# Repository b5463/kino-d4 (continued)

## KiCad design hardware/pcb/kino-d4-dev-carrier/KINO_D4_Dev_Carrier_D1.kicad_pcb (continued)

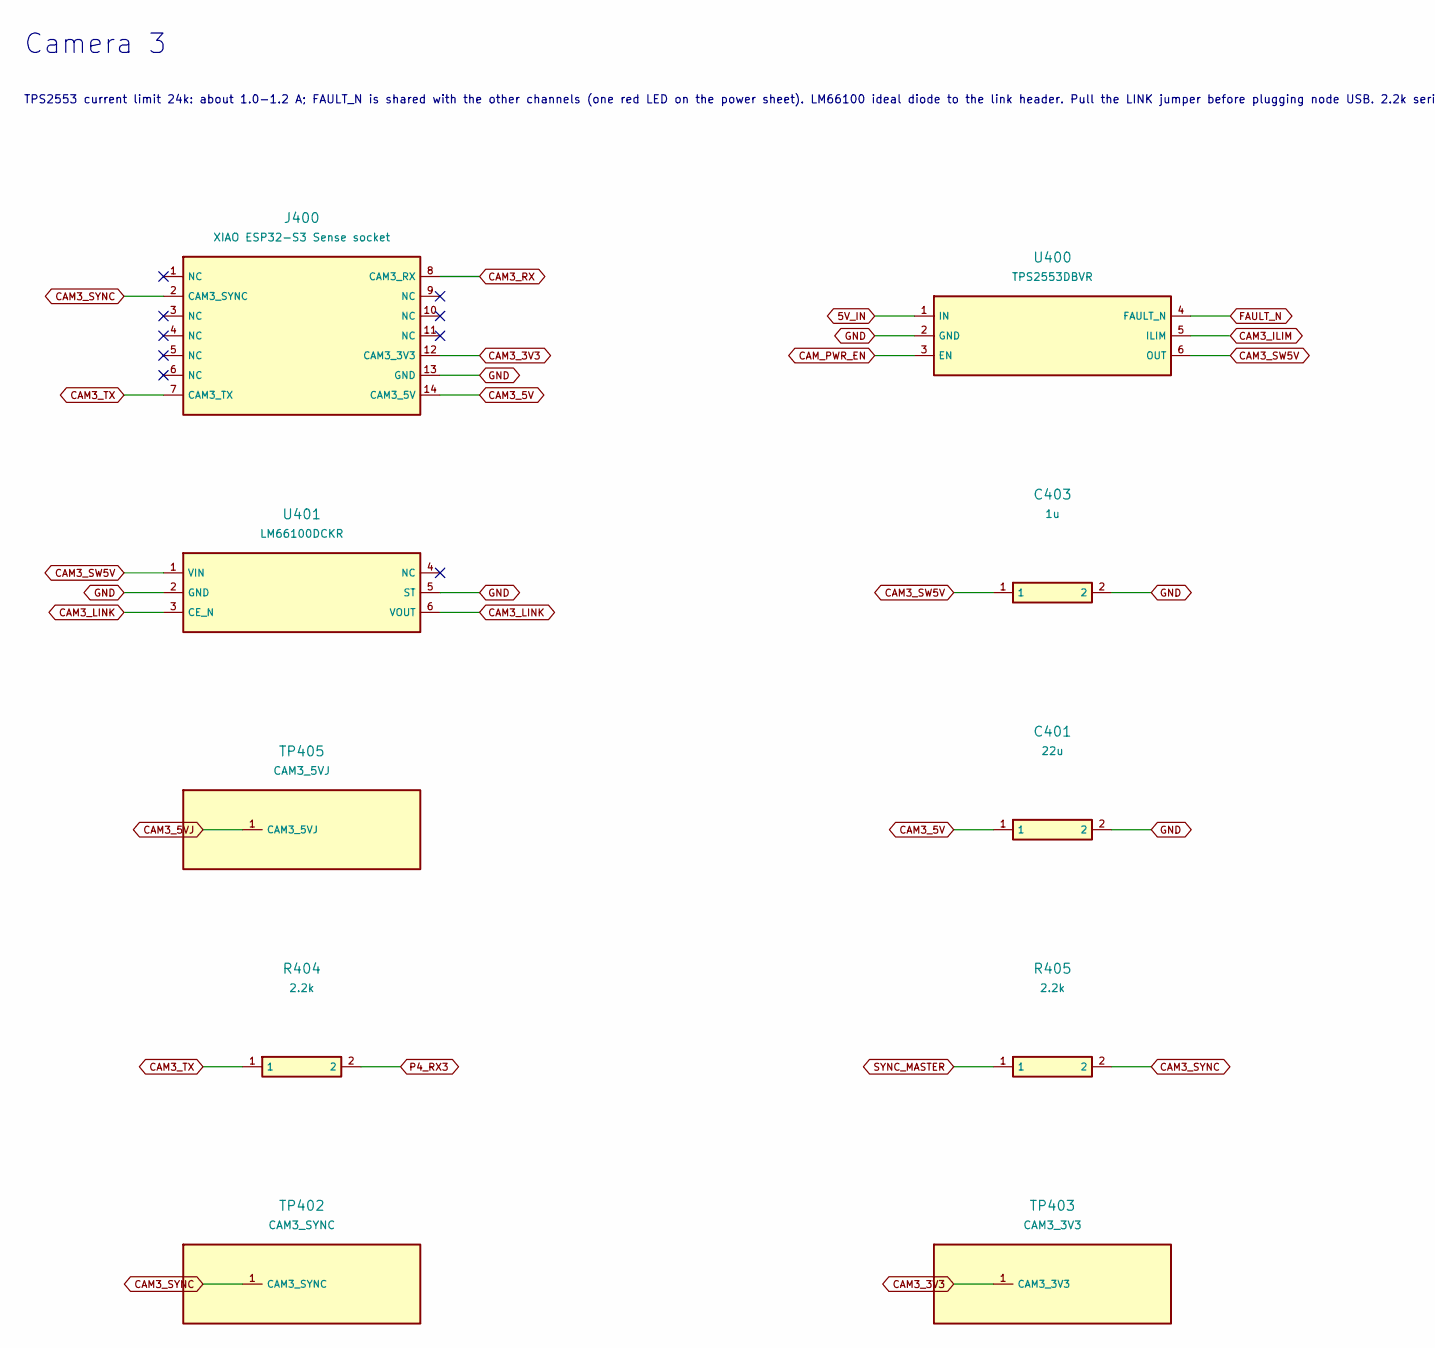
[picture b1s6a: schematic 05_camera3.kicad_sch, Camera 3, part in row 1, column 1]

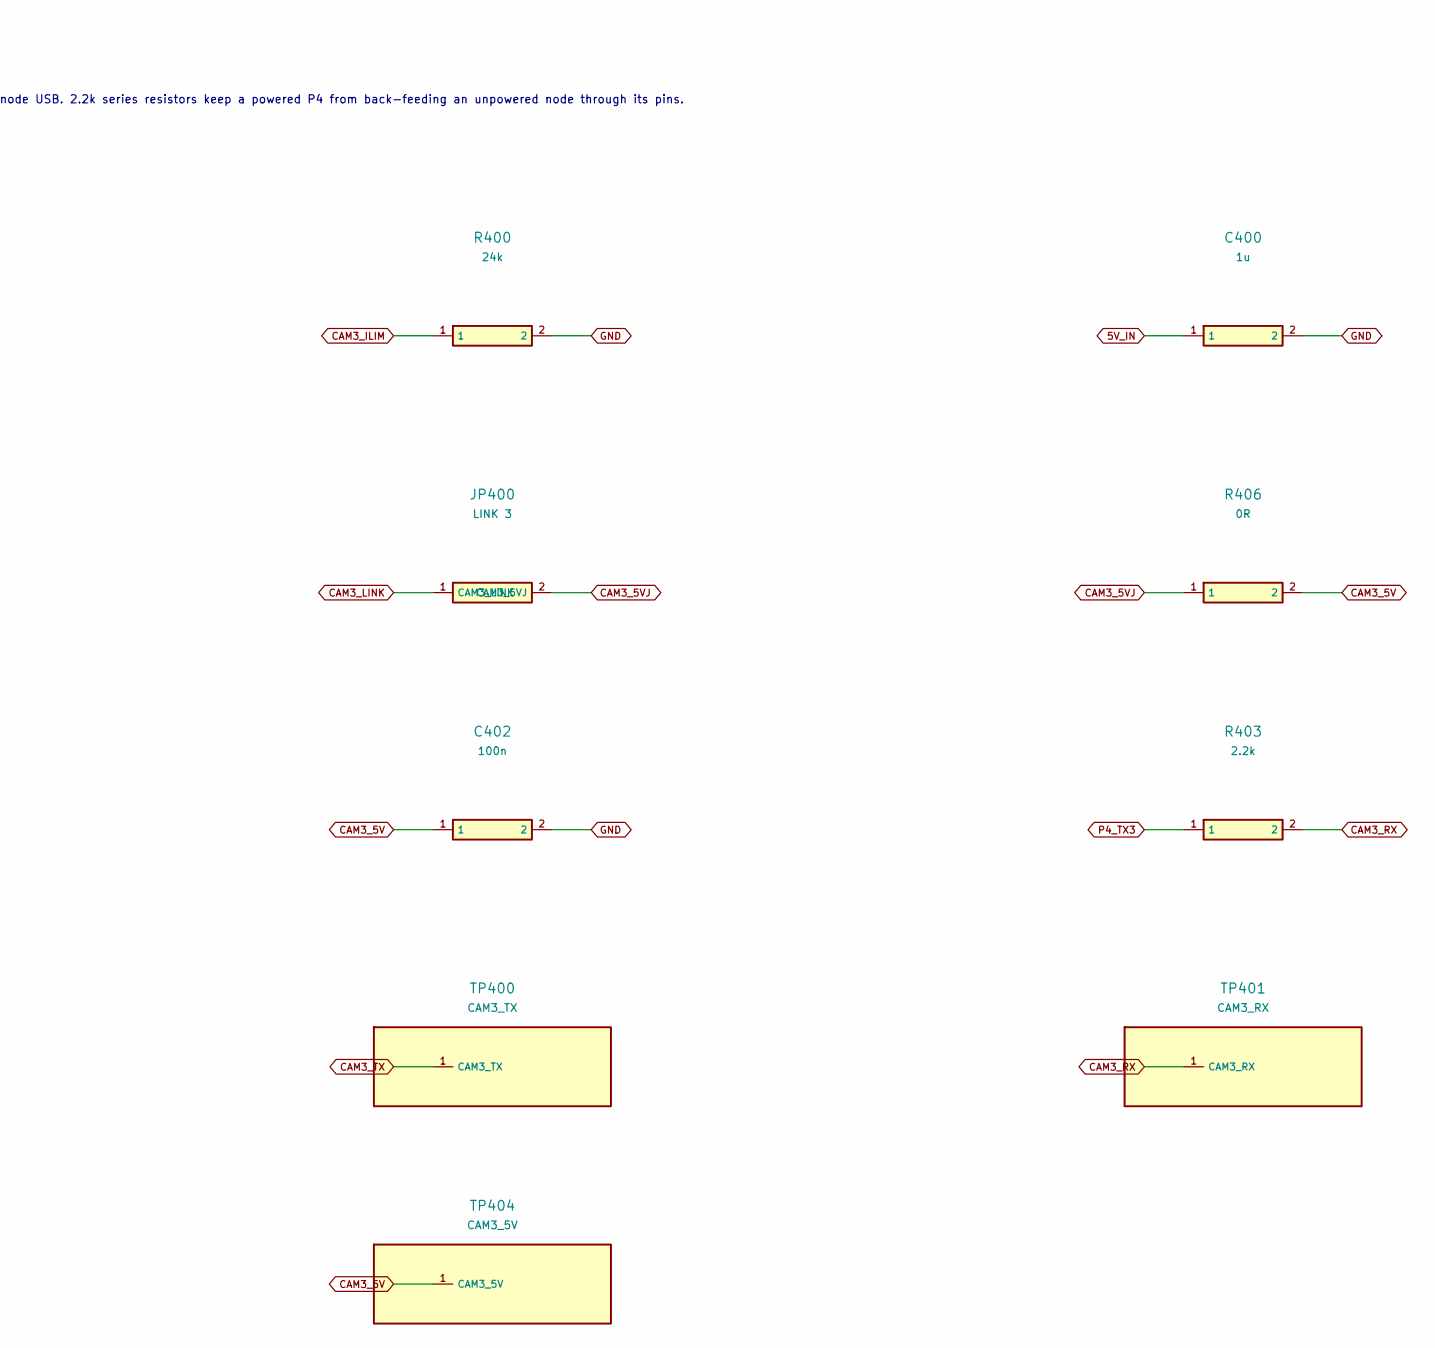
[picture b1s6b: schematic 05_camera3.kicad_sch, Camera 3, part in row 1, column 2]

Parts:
C400, C403: 1u; C_0603_1608Metric; LCSC C15849
C401: 22u; C_0805_2012Metric; LCSC C45783
C402: 100n; C_0603_1608Metric; LCSC C14663
J400: XIAO ESP32-S3 Sense socket; XIAO_Socket_15.24mm
JP400: LINK 3; PinHeader_1x02_P2.54mm_Vertical
R400: 24k; R_0603_1608Metric; LCSC C23352
R403, R404, R405: 2.2k; R_0603_1608Metric; LCSC C4190
R406: 0R; R_0603_1608Metric; LCSC C21189
TP400: CAM3_TX; TestPoint_Pad_D1.5mm
TP401: CAM3_RX; TestPoint_Pad_D1.5mm
TP402: CAM3_SYNC; TestPoint_Pad_D1.5mm
TP403: CAM3_3V3; TestPoint_Pad_D1.5mm
TP404: CAM3_5V; TestPoint_Pad_D1.5mm
TP405: CAM3_5VJ; TestPoint_Pad_D1.5mm
U400: TPS2553DBVR; SOT-23-6; LCSC C55266
U401: LM66100DCKR; SOT-363_SC-70-6; LCSC C2869734

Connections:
5V_IN: C400.1, U400.1 (IN); also elsewhere on the board
CAM3_3V3: J400.12 (CAM3_3V3), TP403.1
CAM3_5V: C401.1, C402.1, J400.14 (CAM3_5V), R406.2, TP404.1
CAM3_5VJ: JP400.2 (CAM3_5VJ), R406.1, TP405.1
CAM3_ILIM: R400.1, U400.5 (ILIM)
CAM3_LINK: JP400.1 (CAM3_LINK), U401.3 (CE_N), U401.6 (VOUT)
CAM3_RX: J400.8 (CAM3_RX), R403.2, TP401.1
CAM3_SW5V: C403.1, U400.6 (OUT), U401.1 (VIN)
CAM3_SYNC: J400.2 (CAM3_SYNC), R405.2, TP402.1
CAM3_TX: J400.7 (CAM3_TX), R404.1, TP400.1
CAM_PWR_EN: U400.3 (EN); also elsewhere on the board
FAULT_N: U400.4 (FAULT_N); also elsewhere on the board
GND: C400.2, C401.2, C402.2, C403.2, J400.13 (GND), R400.2, U400.2 (GND), U401.2 (GND), U401.5 (ST); also elsewhere on the board
P4_RX3: R404.2; also elsewhere on the board
P4_TX3: R403.1; also elsewhere on the board
SYNC_MASTER: R405.1; also elsewhere on the board

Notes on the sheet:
Camera 3
TPS2553 current limit 24k: about 1.0-1.2 A; FAULT_N is shared with the other channels (one red LED on the power sheet). LM66100 ideal diode to the link header. Pull the LINK jumper before plugging node USB. 2.2k series resistors keep a powered P4 from back-feeding an unpowered node through its pins.

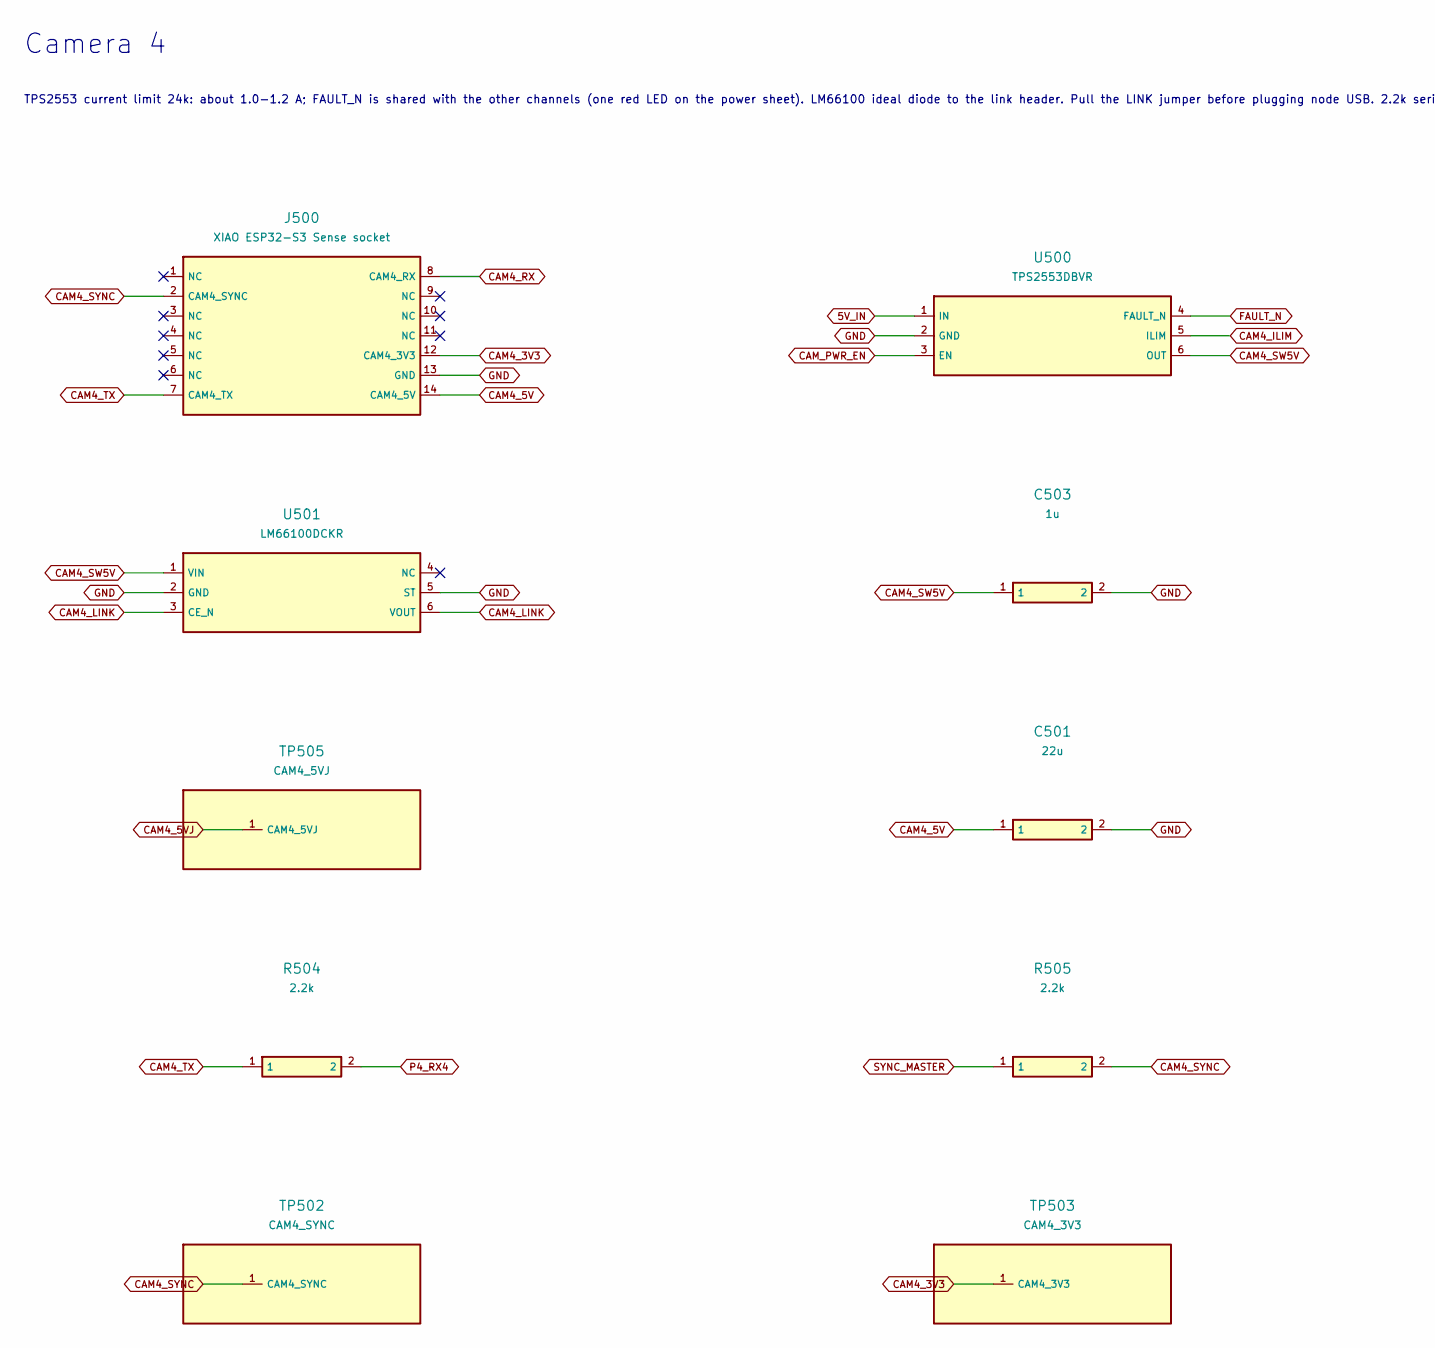
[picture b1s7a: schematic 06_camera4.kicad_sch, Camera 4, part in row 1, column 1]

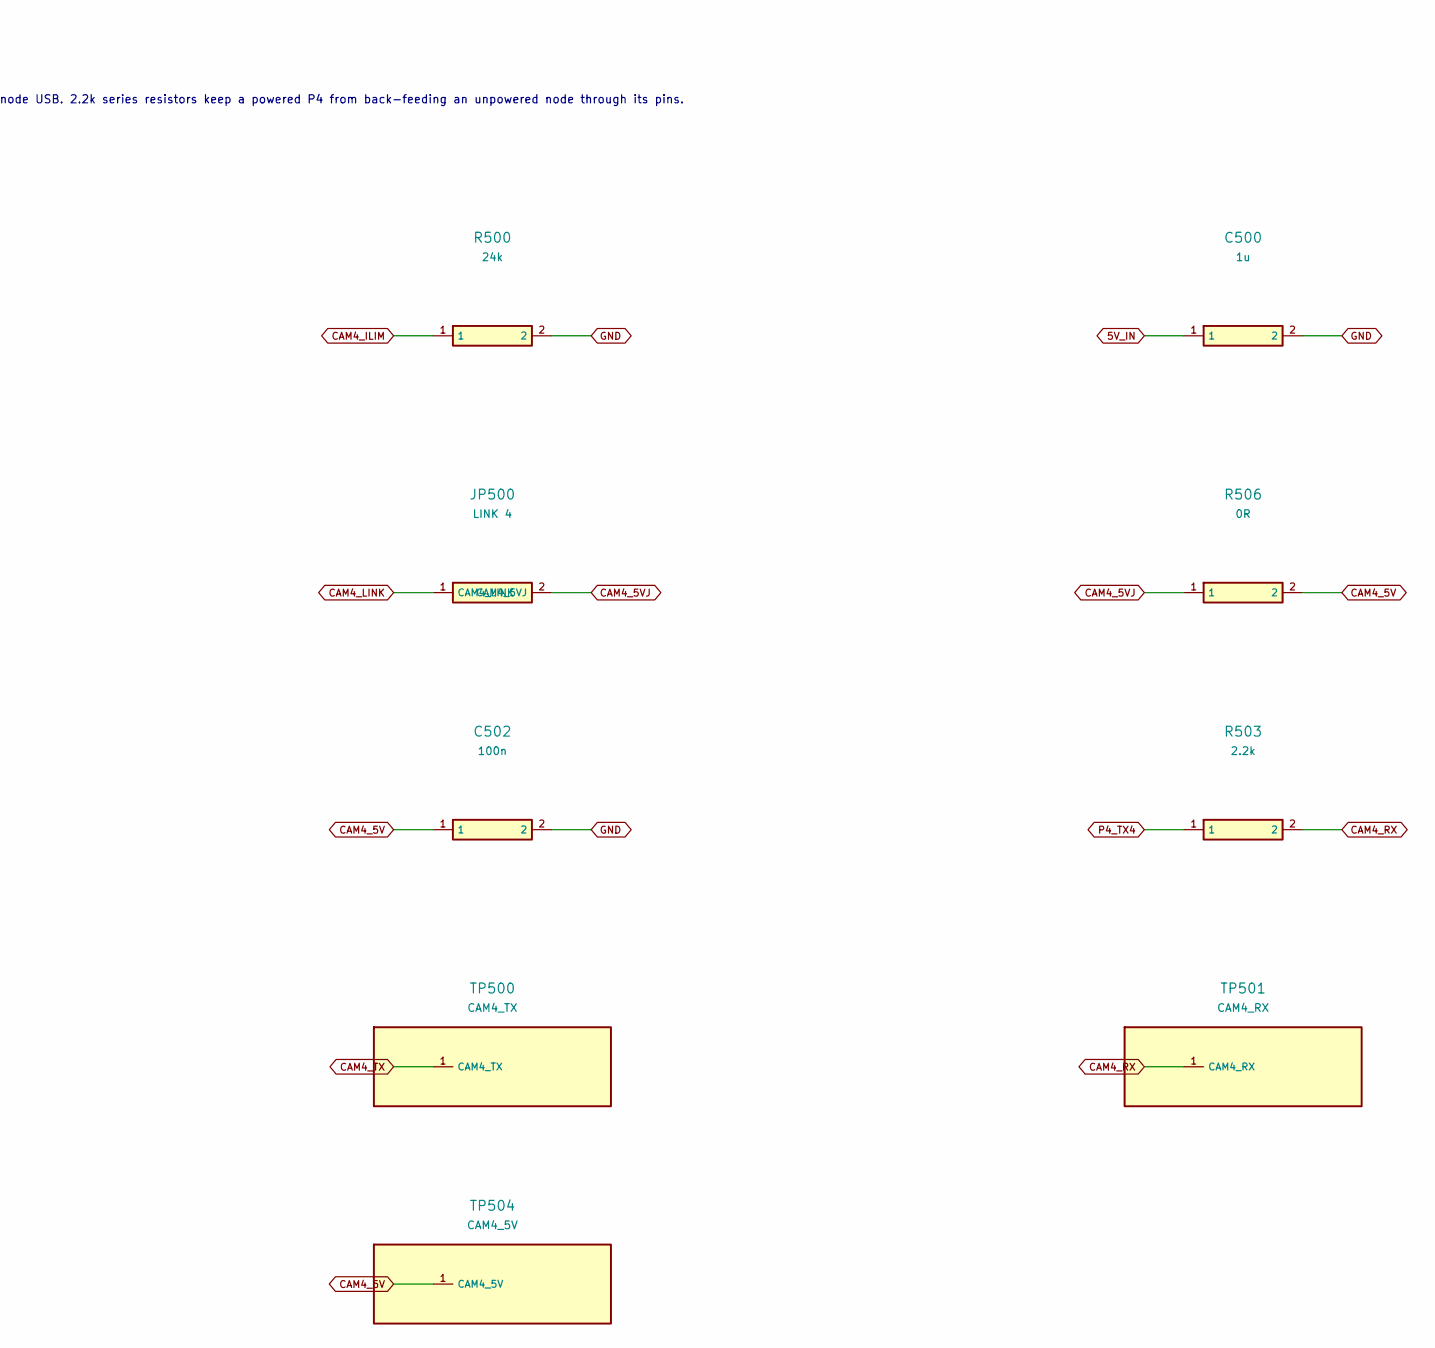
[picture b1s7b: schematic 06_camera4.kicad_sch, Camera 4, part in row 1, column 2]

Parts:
C500, C503: 1u; C_0603_1608Metric; LCSC C15849
C501: 22u; C_0805_2012Metric; LCSC C45783
C502: 100n; C_0603_1608Metric; LCSC C14663
J500: XIAO ESP32-S3 Sense socket; XIAO_Socket_15.24mm
JP500: LINK 4; PinHeader_1x02_P2.54mm_Vertical
R500: 24k; R_0603_1608Metric; LCSC C23352
R503, R504, R505: 2.2k; R_0603_1608Metric; LCSC C4190
R506: 0R; R_0603_1608Metric; LCSC C21189
TP500: CAM4_TX; TestPoint_Pad_D1.5mm
TP501: CAM4_RX; TestPoint_Pad_D1.5mm
TP502: CAM4_SYNC; TestPoint_Pad_D1.5mm
TP503: CAM4_3V3; TestPoint_Pad_D1.5mm
TP504: CAM4_5V; TestPoint_Pad_D1.5mm
TP505: CAM4_5VJ; TestPoint_Pad_D1.5mm
U500: TPS2553DBVR; SOT-23-6; LCSC C55266
U501: LM66100DCKR; SOT-363_SC-70-6; LCSC C2869734

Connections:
5V_IN: C500.1, U500.1 (IN); also elsewhere on the board
CAM4_3V3: J500.12 (CAM4_3V3), TP503.1
CAM4_5V: C501.1, C502.1, J500.14 (CAM4_5V), R506.2, TP504.1
CAM4_5VJ: JP500.2 (CAM4_5VJ), R506.1, TP505.1
CAM4_ILIM: R500.1, U500.5 (ILIM)
CAM4_LINK: JP500.1 (CAM4_LINK), U501.3 (CE_N), U501.6 (VOUT)
CAM4_RX: J500.8 (CAM4_RX), R503.2, TP501.1
CAM4_SW5V: C503.1, U500.6 (OUT), U501.1 (VIN)
CAM4_SYNC: J500.2 (CAM4_SYNC), R505.2, TP502.1
CAM4_TX: J500.7 (CAM4_TX), R504.1, TP500.1
CAM_PWR_EN: U500.3 (EN); also elsewhere on the board
FAULT_N: U500.4 (FAULT_N); also elsewhere on the board
GND: C500.2, C501.2, C502.2, C503.2, J500.13 (GND), R500.2, U500.2 (GND), U501.2 (GND), U501.5 (ST); also elsewhere on the board
P4_RX4: R504.2; also elsewhere on the board
P4_TX4: R503.1; also elsewhere on the board
SYNC_MASTER: R505.1; also elsewhere on the board

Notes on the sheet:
Camera 4
TPS2553 current limit 24k: about 1.0-1.2 A; FAULT_N is shared with the other channels (one red LED on the power sheet). LM66100 ideal diode to the link header. Pull the LINK jumper before plugging node USB. 2.2k series resistors keep a powered P4 from back-feeding an unpowered node through its pins.

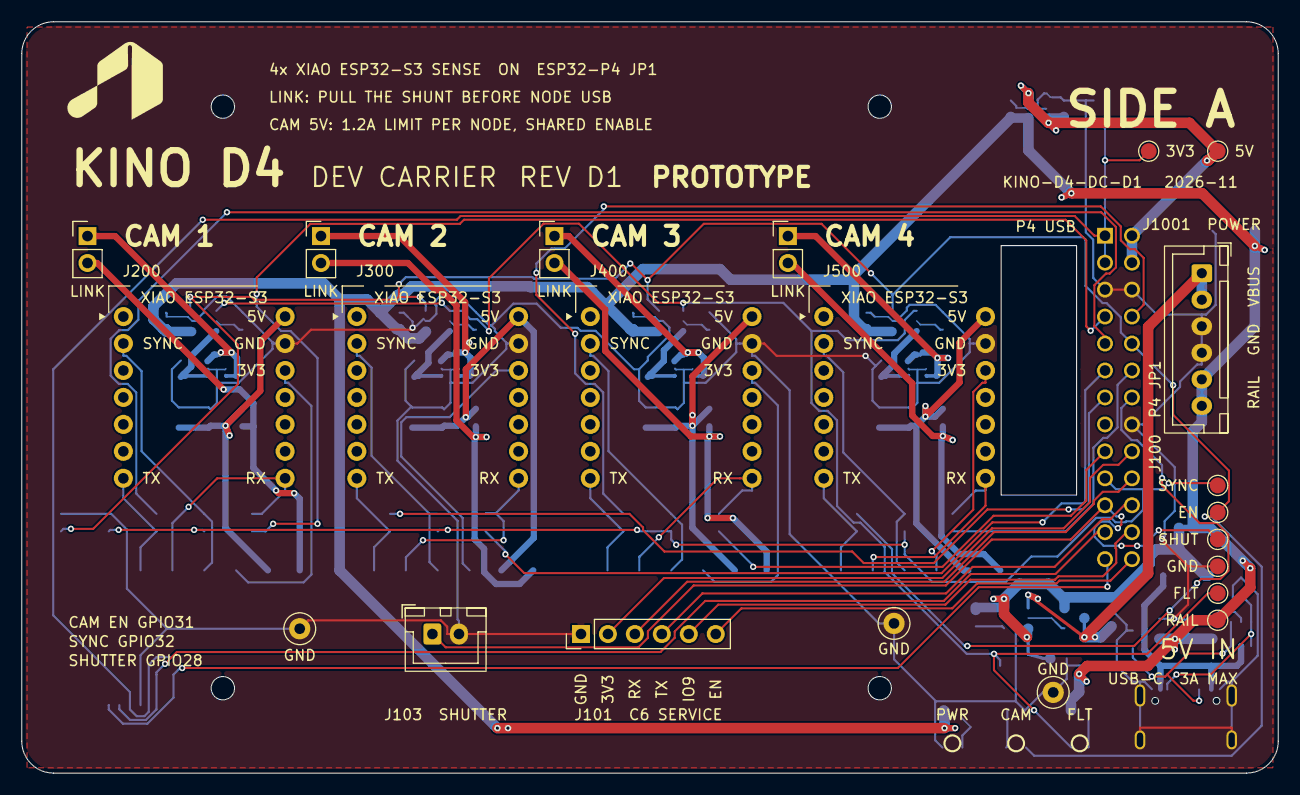
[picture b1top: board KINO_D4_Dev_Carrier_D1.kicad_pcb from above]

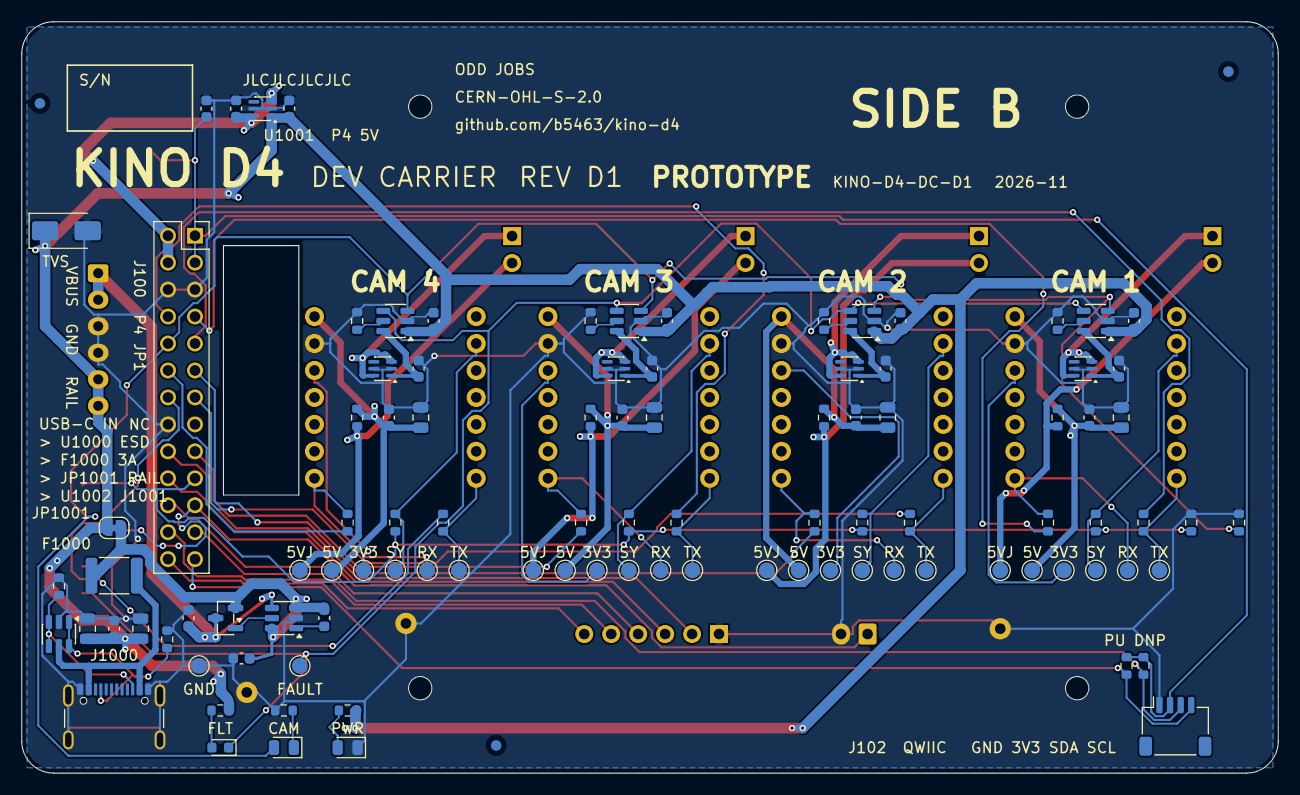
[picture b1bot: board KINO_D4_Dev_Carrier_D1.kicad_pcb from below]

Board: 2 copper layers, 118.4 x 70.8 mm, 130 parts (104 on the bottom side), 69 nets.

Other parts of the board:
H1, H2, H3, H4: M2; MountingHole_2.2mm_M2

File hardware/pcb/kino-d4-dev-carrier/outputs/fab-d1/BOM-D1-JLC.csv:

Comment,Designator,Footprint,LCSC Part #,Manufacturer Part,Quantity,JLC library
100n,"C100,C1002,C202,C302,C402,C502",C_0603_1608Metric,C14663,CC0603KRX7R9BB104,6,basic
22u,"C1000,C1001,C201,C301,C401,C501",C_0805_2012Metric,C45783,CL21A226MAQNNNE,6,basic
1u,"C1005,C1006,C1007,C1003,C1004,C200,C203,C300,C303,C400,C403,C500,C503",C_0603_1608Metric,C15849,CL10A105KB8NNNC,13,basic
LED green,"D1000,D1001",LED_0805_2012Metric,C2297,KT-0805G,2,basic
LED red,D1002,LED_0603_1608Metric,C2286,KT-0603R,1,basic
SMAJ5.0A,D1003,D_SMA,C10758,SMAJ5.0A,1,extended
USB-C 5V,J1000,USB_C_GCT_USB4105_KINO_GND0.05,C3020560,GCT USB4105-GF-A,1,extended
QWIIC 3V3 I2C,J102,JST_SH_SM04B-SRSS-TB_1x04-1MP_P1.00mm_Horizontal,C160404,SM04B-SRSS-TB(LF)(SN),1,extended
IRLML0030TRPBF,Q1000,SOT-23,C67272,IRLML0030TRPBF,1,extended
4.7k,"R100,R101",R_0603_1608Metric,C23162,0603WAF4701T5E,2,basic
5.1k,"R1000,R1001",R_0603_1608Metric,C23186,0603WAF5101T5E,2,basic
1k,"R1002,R1004",R_0603_1608Metric,C21190,0603WAF1001T5E,2,basic
470R,R1003,R_0603_1608Metric,C23179,0603WAF4700T5E,1,basic
24k,"R200,R300,R400,R500",R_0603_1608Metric,C23352,0603WAF2402T5E,4,basic
2.2k,"R203,R204,R205,R303,R304,R305,R403,R404,R405,R503,R504,R505",R_0603_1608Metric,C4190,0603WAF2201T5E,12,basic
0R,"R206,R306,R406,R506",R_0603_1608Metric,C21189,0603WAF0000T5E,4,basic
USBLC6-2SC6,U1000,SOT-23-6,C7519,USBLC6-2SC6,1,extended
LM66100DCKR,"U1001,U201,U301,U401,U501",SOT-363_SC-70-6,C2869734,LM66100DCKR,5,extended
LM74700QDBVRQ1,U1002,SOT-23-6,C2941042,LM74700QDBVRQ1,1,extended
TPS2553DBVR,"U200,U300,U400,U500",SOT-23-6,C55266,TPS2553DBVR,4,extended

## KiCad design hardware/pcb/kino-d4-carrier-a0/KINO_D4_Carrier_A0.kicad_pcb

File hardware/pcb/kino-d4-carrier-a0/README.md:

# KINO D4 carrier A0.2

**Release candidate, 3 October 2026: READY FOR FABRICATION WITH SPECIFIC MANUAL CHECKS.** Fully routed; DRC, ERC and schematic parity clean. Do the checks listed in the [release review](A02-RELEASE.md) before ordering.

Open [KINO_D4_Carrier_A0_2.kicad_pcb](KINO_D4_Carrier_A0_2.kicad_pcb) with its matching project settings. This is the current working board. The supplied [ODD JOBS standard](ODD-JOBS-STANDARD.txt) governs release. The [release review](A02-RELEASE.md) holds the release matrix, the manual checks and the bring-up tests; the 30 September [engineering review](A02-REVIEW.md) is superseded history.

The board has 256 footprints: 80 on the front and 176 on the back, six of them board-only fiducials (three per face). The front carries the four XIAO sockets, the J600 pogo field, the TP100 and TP600-TP602 probe lands, J1100, J1000 and low SMD parts only, so the socketed XIAOs are the tallest parts on it; every cable connector and pin header (J100, J101, J102, J201-J501, J601, J800, J900-J904, J1300) is on the back, the P4 side. The four XIAO sockets keep 22 mm pitch and a 66 mm outer span, with 15.24 mm row centres and 2.54 mm pin pitch. The outline is 117.01 × 69.41 mm. Four 2.2 mm holes target the P4 inner inserts on 61.9 × 54.8 mm centres, with a drawing-derived absolute offset. These XY checks do not validate the assembled enclosure or connector stack.

The [14-sheet schematic](KINO_D4_Carrier_A0.kicad_sch) is the current electrical capture. Historical A0 and A0.1 boards are preserved but no longer match it. Do not use them for fabrication or combine their reports with A0.2.

## Current review files

| File | Purpose |
|---|---|
| [Release review](A02-RELEASE.md) | Release matrix (PASS / FAIL / MANUAL), resolved findings, manual checks before ordering, bring-up tests |
| [Fab package](outputs/fab-a02/) | `fab_a02.py`: Gerbers with job file, Excellon drill, `KINO_D4_Carrier_A0_2-gerbers.zip`, placement file and grouped fab BOM |
| [Assembly front](outputs/A02-ASSEMBLY-FRONT.svg) / [back](outputs/A02-ASSEMBLY-BACK.svg) | References, courtyards and outline; rear view mirrored |
| [Front power detail](outputs/A02-POWER-FRONT.png) / [back power detail](outputs/A02-POWER-BACK.png) | Pack entry, charger and boost region |
| [A0.2 verification](outputs/VERIFICATION-A02.json) / [routing audit](outputs/A02-ROUTING-AUDIT.json) | Counts, geometry and capture-transfer evidence, with board digest |
| [Native DRC](outputs/DRC-A02.json) / [ERC](outputs/ERC-DRAFT.json) | Checker results; no implied manufacturing acceptance |
| [Schematic PDF](outputs/SCHEMATIC-DRAFT.pdf) | 14-sheet capture |
| [BOM](outputs/BOM-DRAFT.csv) / [part selection](design/part_selection.json) / [pin matrix](outputs/PIN_NET_MATRIX.csv) | Manufacturer parts checked against datasheets; battery pack still open |
| [Mounting template](outputs/P4-MOUNTING-TEMPLATE-1TO1.pdf) / [mechanical evidence](MECHANICAL.md) | Print at 100 %; stack and enclosure still unqualified |
| [Printed labels](outputs/A02-PRINTED-LABELS.json) / [assembly references](outputs/A02-ASSEMBLY-LABELS.json) / [unplaced references](outputs/A02-ASSEMBLY-LABELS-UNFINISHED.json) | Label positions; parts without a clear, unambiguous silk position beside the part |
| [Silk text check](outputs/A02-SILK-TEXT.json) | `check_silk_text.py`: text over text, pads, part bodies or silk graphics, crowded or ambiguous references, reading direction |

**Routing status, 3 October 2026 (release pass):** every connection is routed. Native DRC (zones refilled, schematic parity on) reports no violations and no unconnected items; ERC reports none; `verify.py --a02` passes against a freshly exported netlist. 573 vias; 2385 track segments (F 786, In2 414, B 1185). The SYS_RAW battery-to-boost path is now a 3.4-3.9 mm back pour and a 4.6-5.2 mm In2 pour with 19 vias between them and six into L1200 (`power_a02_sys_raw.py`). Five 0.1 mm right-angle wobbles remain inside 0.5-0.8 mm copper (no exposed corner). CAM2_3V3 still takes the long route south of U300 (0.25 mm, light load); CAM_GLOBAL_EN and BOOST_ENABLE are long In2 runs, BOOST_ENABLE now held by R1204 (100k) at the boost end.

Prototype references are on silkscreen (ODD JOBS rule 177) beside their own part: 0.15 mm clear of part outlines, 0.5 mm from other silk text, horizontal text left to right and vertical text bottom to top from its own side (rule 91), 1.0 mm text or 0.8 mm in dense areas, 0.15 mm stroke. A spot more than 0.5 mm nearer another part is not used. After the release pass, 202 of 250 references are on silk; no text overlaps another text, a pad, a part body or a silk graphic (`check_silk_text.py`: 0 findings). The four camera circuits share one offset per role, or the whole group of four goes to Fab. 48 references in the camera, charger and boost clusters (and the DNP R1110) stay on Fab at the part centre and are listed in the unplaced file; they need part spacing, not smaller text. The fiducials keep their references on Fab. Connector, camera and product labels use 1.0 mm text with a 0.15 mm stroke.

## Circuitry

- **Cameras:** four socketed XIAO ESP32-S3 Sense boards with UART/sync isolation buffers, individual current-limited supplies, current monitoring and 0 ohm USB-service power links (JP200-JP500, Vishay CRCW12060000Z0EAHP, desolder before node USB). D8/D9/D10 are shared with the Sense SD interface, and D2 is strap-sensitive.
- **I2C buffer:** U100 (TCA9517) has the carrier bus on its A side, which drives a hard low; the B side's 0.45-0.6 V buffered low faces the P4 bus (P4 VIL 0.825 V). The STUSB4500 (VIL 0.35 V), BQ25798 (0.4 V) and DRV2605L (0.5 V) could not be guaranteed to read the buffered low. Keep the whole bus at 100 kHz (4.7k pull-ups, about 95-150 pF). R100/R101 (2.2k/22k) hold the buffer enable low when JP1 pin 1 is open.
- **P4 link:** the 26-pin P4 connection is a keyed IDC **cable** interface, kept until Guition supplies a JP1 datum for a board-to-board mate. The UART/sync/shutter header map is unchanged; GPIO35/JP1-15 stays unconnected.
- **Power:** USB-C PD sink (STUSB4500), 1S charger (BQ25798), fuel gauge (BQ27441-G1), 5 V boost (TPS61288), 3.3 V buck and a hardware power controller.
  - The USB input survives an unprogrammed STUSB4500, which takes 20 V from a PD charger: D1001 is an SMF22A (22 V standoff), the PD switch FETs are AO4409 (-30 V), R1004 is 10k. Program the NVM for 9 V / 2 A with the 5 V fallback for normal use.
  - The LTC2955-1 EN output is a 2 uA current source; R1204 (100k to SYS_RAW) is the pull-up ADI asks for, so the TPS61288 enable and the PMV16UN load-switch driver (Q1202) see a full logic high.
  - The charger charges whenever VBUS is valid (CE low), inside a 1-60 °C window set by the pack's 103AT-2 thermistor.
  - The gauge shunt is high side, with SRP on the pack side and SRN on the system side.
  - Input current is clamped to 0.15-0.41 A until firmware reads the PD contract, so the board needs its battery to run the P4 and cameras from USB.
  - Off, the board draws 28-46 uA through R1204 plus the controllers' quiescent current.
  - The charger's STAT pin is left open and there is no charge LED (STAT has no layout path out of the charger's power copper). Firmware reads the charge state from the BQ25798 status registers over I2C. The green power LED D1300 stays.
- **Pack entry:** J1100 (JST VH, `- NTC +`) sits on the bottom edge beside the charger. From the pack, F1100 (7 A) and RS700 (5 mΩ) form a 12 mm chain on the front.
- **Sensors and controls:** IMU, backed-up RTC, board-temperature sensor, remote shutter, cover sensor, function button (ESD clamp D903), haptic driver and expansion/service connectors. R105 holds SYNC_MASTER low through the P4's reset.
- **Power links:** JP200-JP500 and JP1200 are 0 ohm links on the front (CRCW1206-HP, 10 A), replacing the 2.54 mm headers and shunts: flat, reachable with the carrier on the P4, rated for the current. Desolder to open.
- **Test field:** J600 is an asymmetric 12-pad **sense/test** field, not a power-injection connector. Do not drive the enable nodes against the expander. Pads 9-11 are unconnected: CAM2_EN, CAM3_EN and CAM4_EN are probed at front lands TP600-TP602 beside their lines at the top of the board (CAM1_EN stays on pad 8). TP100 (P4 3V3 test) is a front land beside J100 pin 1.
- **Expander map:** U600 (TCA9539) port 1, P1.0-P1.7 (pins 13-20): IMU_INT, RTC_INT_N, SOFT_KILL, unused, POWER_INT_N, FN_N, HAPTIC_EN, COVER_N. P1.3 is not connected; configure it as an input. Firmware must follow this map.
- **Flash provision:** J601/R605 are DNP provisions for an **external flash driver**. There is no FLASH_EN GPIO or flash-energy supply.

I2C addresses: PAC1954 0x10, STUSB4500 0x28, TMP117 0x48, RV-3028 0x52, BQ27441 0x55, DRV2605L 0x5A, LSM6DSOX 0x6A, BQ25798 0x6B, TCA9539 0x74. P4 touch at 0x5D stays on the host side of the buffer. [`firmware/p4/main/kino_carrier_a02.h`](../../../firmware/p4/main/kino_carrier_a02.h) holds these addresses, the expander map, the PAC1954 channel map and the charger status field as constants. Existing firmware does not start the carrier's power controls, charger policy or gauge calibration.

## Manufacturing and assembly status

Process: four layers, 1.6 mm, **1 oz copper on all four layers** (set in the board stackup and the Gerber job file; inner 1 oz is not JLCPCB's default), black mask, white silk, ENIG, JLCPCB-class. `design/fab_a02.py` writes the [fab package](outputs/fab-a02/): Gerbers (silk clipped at mask openings) with the job file, Excellon drill (plated and non-plated apart) with maps, one zip for upload, the placement file (both sides, DNP and board-only items left out) and a fab BOM grouped by part number. Fab and assembly notes, the via-in-pad list and the order options are in the [release review](A02-RELEASE.md). Both faces are assembled: the bottom (P4 side) carries most SMD parts including the heavy XAL7070 boost inductor, the XIAO sockets and J1100 are through-hole on the front, the pin headers and J100 through-hole on the back.

Battery selection, retention and the assembled body are not built or verified. The XAL7070 boost inductor (7.0 mm) and the JST VH connector set the tallest parts on their faces. The XIAOs use external antennas; their antenna and cable clearance must be defined in the enclosure. Keep the P4 battery connector unused. USB/P4/carrier source coexistence still needs measurement; the removable power links are service provisions, not automatic backfeed protection.

## Editing and regeneration

The native A0.2 PCB is authoritative for placement and routing. `design/circuit.py` defines the capture and `design/mechanical.py` the envelope and datums. **Do not run the full build or placement seed against current work**: they reset placement and routing.

Change scripts, in the order they were applied:
- **Earlier A0.2 changes:** `rework.py`, `route_a02.py`, `spread_a02_*.py`, `refine_a02_placement.py`, `add_a02_interfaces.py`, `finish_a02.py`.
- **Charger, thermistor and inductors (0.1.8):** `a02_power_rev.py`.
- **Gauge, fuse and CC protection:** `a02_gauge_rev.py`.
- **Pack entry:** `pack_placement.py`, then `route_pack_entry.py`.
- **USB VBUS:** `route_usb_vbus.py`.
- **PMID capacitors:** `route_pmid.py`.
- **Boost supply:** `route_boost_input.py`.
- **Inductor keepouts:** `switch_keepouts.py`.
- **Residual DRC items:** `a02_drc_fixes.py`.
- **Labels:** `pack_labels.py`, `assembly_labels.py --prototype-silk`, then `check_silk_text.py` (exits 1 on any finding). KiCad's silk_overlap check does not compare one footprint's reference with another's.
- **Routing pass, 2 October 2026:**
  1. `route_a02_gaps.py` (charger VBUS corner, U800 supply, boost sense tap), `gnd_stitch.py`.
  2. `grid_router.py` pass, `apply_routes.py`.
  3. `route_a02_charger_escapes.py`: BQ25798 left-column escapes; moves C1119, C1103, C1100, R1104, R1105.
  4. `tidy_a02_dangling.py`, `a02_pad_connections.py`.
  5. `route_a02_sync_bus.py`: SYNC bus from y 19.4 to y 41.05 at the buffers.
  6. `rip_camera_row.py`, then `grid_router.py` with `GR_ORDER=argv` (FAULT_N, EN, REQ, SHUNT_OUT, SYS_5V).
  7. `route_a02_camera_bus.py remove`, `add`, `verify`: In2 control lanes north of the headers.
  8. `place_a02_u600.py place`, `rip`: U600 turned 180 degrees, C601 beside pin 24; `drop_dangling.py`; router.
  9. `place_a02_brand.py`: maker mark moved onto clear pour below J901.
  10. `tidy_routes.py`, run last.
- **External connections to the back, 2 October 2026:**
  1. `place_a02_j100.py place`, `rip`, `add`: J100 on the back in its outline; P4_5V redrawn at 1.2 mm.
  2. `place_a02_backside.py flip`, then `free_spot.py` for J902 and J904, `tofront`, `rip`: headers and JST connectors to the back; the haptic driver cluster, Q1300, R1300, R1301 and R1304 to the front in their place.
  3. `fp_a02_link_1206.py`, `circuit.py` change, `regenerate_capture.py`, netlist / ERC / PDF, `place_a02_links.py`: JP links become 0 ohm links on the front.
  4. `route_a02_p4_feed.py rip`, `add`: P4_5V_ISO as a 2.0 mm In2 run with three vias per layer change.
  5. `clear_a02_backside.py move`, `rip`; `drop_dangling.py`: courtyard and copper conflicts cleared, J601 0.65 mm north.
  6. `place_a02_labels.py`, `assembly_labels.py --prototype-silk`, `check_silk_text.py`: connector labels on the back silkscreen, references beside their parts, silk text check.
- **SYS_5V, 3 October 2026:**
  1. `route_a02_sys5v.py rip`, `add`, `link-rip`, `link-add`: trunk, drops, riser and feed; camera 1 SHUNT_OUT via, IMU_INT middle and the U700 SENSE+ tie removed for it.
  2. `grid_router.py SYS_5V` with `GR_SKIP_REF=U700`, `apply_routes.py`, `tidy_routes.py`: U1201 and J600 branches.
  3. `straighten_a02_j600.py`: the J600 branch as one straight run.
- **Signal pass, 3 October 2026:** `grid_router.py` over every open net except the camera header-socket GPIO, `GR_SKIP_REF=U700`; `apply_routes.py`; `tidy_routes.py`. 195 -> 114 unconnected; six routes at minimum clearance (RTC_BACKUP, P4_SCL, CHARGE_LED_A, CAM3_REQ, MOTOR_N, CAM1_EN) for review. Through-hole pads now also allow 45-degree exits in the router.
- **Camera GPIO, 3 October 2026:** `route_a02_cam_gpio.py clear <k>` for k = 4, 3, 2, 1, DRC and `drop_dangling.py` until stable, then `add <k>`: the eight header-to-socket GPIO lines of each camera as one identical In2 fan-out (eight 1.27 mm lanes, 45-degree fans, no crossings). `plan <k>` reports what is in the way. The nets it opens (camera EN, SYNC, SHUNT_OUT, P4_BUS_EN, MB_3V3 pieces) go back to the grid router.
- **Second router pass, 3 October 2026:** `grid_router.py` over all open nets (`GR_SKIP_REF=U700`), `apply_routes.py`, `tidy_routes.py`: 101 -> 75. P4_BUS_EN is at minimum clearance (review).
- **Ground fixes, 3 October 2026:** five GND pins reached no ground (U900.4/.8 after the haptic driver moved to the front, U701.3, C1101.2, U1201.1). `gnd_stitch.py`; `gnd_pad_vias.py U701.3 'U1201.1>U1201.9'` (U1201 pin 1 to its exposed pad, as in TI's layout); `rip_box.py CHG_REGN 92.5 56.5 97.0 61.0` (a route that circled C1101) then `gnd_pad_vias.py C1101.2` and the router for CHG_REGN; `rip_box.py` for REMOTE_ACTIVE and HAPTIC_REG under U900, `route_a02_u900_gnd.py`, the router for both nets, `gnd_stitch.py`. GND has no open connection; `gnd_islands.py` still lists the U701.3 and U1201.1 fragments because it looks only for a via inside a fragment, not for a track out of it.

- **U700 and Kelvin pairs, 3 October 2026:**
  1. `place_a02_u700.py rip`, `place`: the PAC1954 U700 moves to the front between the camera 2 and 3 headers, centre (58.75, 15.5), with C700 and R700 beside it and C701 on the back; copper on their pads and three runs in the way removed.
  2. `route_a02_kelvin.py clear`, then DRC and `drop_dangling.py --keep <nets with deliberate stubs>` until stable, then `add`: eight 0.15 mm sense lines at 0.32 mm pitch from the inner pad corners of RS200-RS500 to U700, plus U700's GND, MB_3V3 and PAC_ADDR copper. The CAM2_5V and CAM3_5V_ISO vias move. `add` sets the moved vias' nets back, because a save in between can give a via with nothing of its own net attached the pour's net.
  3. `check_a02_kelvin.py`: each sense line touches only its shunt pad and its U700 pin.
  4. `fp_a02_pac1954.py`, `circuit.py` change, `regenerate_capture.py`, netlist / ERC / PDF, `place_a02_u700.py place`: U700 on a project copy of the VQFN-16 land whose pin 1 triangle sits beside the pin 1 corner (the stock one lay on C700's pad).
- **Bus slot, edges and expanders, 3 October 2026** (hand scripts on `handroute.py`; each runs `rip`, `place` where it has one, then `add`, as separate processes):
  1. `route_a02_local_fixes.py`: USB_CC2 out of U1000 (a VBUS via moved), CHG_REGN's missing piece and an In2 link that frees R1107, CHG_TS, POWER_KILL_N under U802 / C803, a straight PACK_FUSED sense exit.
  2. `route_a02_p4_rx4.py`: P4_RX4 back in its F bus lane (y 20.6) with its J100 tap; POWER_INT_N, CAM2_5V and CAM2_5V_ISO cross the band on In2 in one piece; camera 3's 3V3 runs as camera 1's and shares the header row gap with CAM3_FAULT_N at 0.15 mm; TX3, TX1 and RX2 no longer run past their taps.
  3. `place_a02_remote.py dry` / `rip` / `place`, `route_a02_remote.py`: the remote dry-contact chain (D900, R903, R904, C904, U901, C905, R905, Q900) beside J903 and D902 beside J902 (ESD at the connector, ODD JOBS 24).
  4. `route_a02_left_edge.py`: the four C6 service lines up the left edge and along the top edge into J101; SHUTTER_N from Q900 down the left edge on B into J100 pin 21.
  5. `route_a02_u601.py`: C602 beside U601's VCC pin, CAM_GLOBAL_EN tied once under the package, CAM1_EN, CAM3_EN, CAM3_REQ and CAM4_EN out of U601 (CAM3_EN down the In2 column between the SYS_5V riser and camera 3's fan).
  6. `route_a02_test_legs.py`: J600 test legs (CAM1_EN's leg to U201's EN node).
  7. `grid_router.py` (`GR_OUT` names an output; `apply_routes.py` takes the same variable) between the steps for the short links.
  8. `route_a02_mb3v3.py` (3.3 V to the moved remote chain), `route_a02_top_lanes.py` (U600 port 1 lines along the top edge), `route_a02_u900.py` (MOTOR_P out of the haptic driver).
  9. `circuit.py` change, `regenerate_capture.py`, netlist / ERC / PDF, `route_a02_u600.py`, `route_a02_bundle_ends.py`: U600 port 1 in layout order and the camera 1/2 channel bundle (F rows, In2 down between the sockets).
  10. `circuit.py` change (R700 ADDRSEL strap dropped, pin 6 to the exposed pad), `place_a02_u700.py place`, `route_a02_u700_i2c.py`: I2C into U700.
- **I2C and power side, 3 October 2026** (same hand-script pattern):
  1. `route_a02_u801.py` (RTC pins out west, R800 moved), `route_a02_i2c.py` (SCL/SDA between the west cluster, U801, U800 and the power side), `route_a02_u1100.py` (charger pocket: BAT_PROTECTED strap to F, CE / SCL / SDA out south, R1110 and R1102 moved), `route_a02_u701.py` (gauge I2C, C702 between the USB-C shield pins, U1000 PD_DISCH / SDA), `route_a02_u900_sda.py`.
  2. `route_a02_gauge.py` (R701 and R702 beside U701), `route_a02_u1000_top.py` (R1004 above pin 16, C1000 moved), `route_a02_stat.py` and `circuit.py` (U600 P1.3 unused), `route_a02_pb_corner.py` (U1300 PB / EN escapes; D1300 and R1303 moved; D1301, R1304, R1109 and TP1100 removed with the charge LED).
  3. `circuit.py` change, `add_a02_enable_tps.py`, `route_a02_enable_tps.py`: TP600-TP602 for CAM2-CAM4_EN in place of J600 pads 9-11. `route_a02_u1200_en.py`: U1200 EN to a via (MB_3V3 spur and SYS_RAW riser shifted).
- **Last opens and finish, 3 October 2026:**
  1. `route_a02_j100.py` (TP100 to the front beside J100), `route_a02_p4_sense.py` (P4_3V3_SENSE down the west edge on B), `route_a02_p4_bus_en.py` (U100 EN and the R100/R101 divider onto the buffer chain on In2), `route_a02_cam_global_en.py` (J100 pin 10 to U601 on In2 along the top), `grid_router.py CAM2_3V3` + `apply_routes.py`, `route_a02_boost_en.py` (U1200 EN on In2 round SYS_RAW to Q1202), `route_a02_cam2_fault.py` (U301 FAULT to U600 pin 9 on B, In2 under U600; R603's GND pad linked to C701), `route_a02_gnd_u600.py` (U600 pin 21 via).
  2. `gnd_stitch.py`, `tidy_routes.py`, `chamfer_a02_corners.py` (right-angle bends on locked copper).
  3. `place_a02_c904.py`: C904 out of H1's fastener square (verify.py), vertical below R904.
  4. `assembly_labels.py --prototype-silk`, `check_silk_text.py`; DRC; netlist / ERC / PDF re-exported; `verify.py --a02`, `routing_audit.py --a02`.
  CAM2_FAULT_N had no route the grid router could find within its budget; `GR_DEBUG` masks showed one corridor, which the hand script follows.

- **Release pass, 3 October 2026** (hand scripts on `handroute.py` run `rip`, `place` where they have one, then `add`, as separate processes):
  1. `place_a02_r603_c701.py` (CAM2_FAULT_N no longer passes between passive pads), `gnd_stitch.py` (no stitching via in or touching a GND pad), `fix_a02_via_in_pad.py`, `silk_a02_camera_labels.py`.
  2. `add_a02_fiducials.py`: three fiducials per face, board-only, 1.0 mm pad clearance.
  3. `circuit.py` changes, `regenerate_capture.py`, `release_a02_usb_pd.py` (TP1001 removed, U1000 pin 20 open), `sync_a02_values.py` (board values from the capture): D1001 SMF22A, R1004 10k, AO4409, PMV16UN, R100/R101, BOM text.
  4. `route_a02_scl_l1200.py`: I2C_SCL out from under the L1200 corner on In2.
  5. `fix_a02_socket_mask.py`: mask openings on the XIAO socket pads (the footprint generator had dropped them; `build.py` and the library are fixed too).
  6. `fix_a02_via_webs.py`: vias out of and away from pads (CAM1_EN at U201, C901, CHG_PMID, CHG_BTST1, U701, a dead CAM3_5V_ISO via).
  7. `swap_a02_u100.py`: the TCA9517 sides swapped, its four I2C connections redrawn; `gnd_stitch.py`.
  8. `add_a02_release_parts.py`, `release_a02_parts_route.py`: R105, R1204, D903.
  9. `power_a02_sys_raw.py` (`rip`, `add`, `pour`): SYS_RAW pours and stitching.
  10. `fix_a02_u1200_marks.py`: U1200 body outline and pin-1 dot.
  11. `mark_a02_release.py`: CARRIER A0.2 / 2026-10 lines, P4 JP1 label, S/N box.
  12. Final review fixes: `fix_a02_peg_via.py` (GAUGE_1V8 via 0.52 mm from the J1000 peg), `assembly_test_pads.py` (outlines of removed test lands dropped), `sync_a02_values.py`, `silk_a02_widths.py` (legend lines and strokes to 0.15 mm), `fp_a02_pac1954.py` then `silk_a02_u700_mark.py` (U700 pin-1 triangle clear of C700), `assembly_labels.py --prototype-silk` (ambiguous camera groups and R1003/R1110 to Fab, C1105 above its part, 1 mm silk-free ring round the fiducials), `check_silk_text.py`.
  13. DRC, netlist / ERC / PDF, `resistor_selection.py`, `verify.py --a02`, `routing_audit.py --a02`, `fab_a02.py`.
  14. After release, same day: `place_a02_connector_row.py` (`rip`, `place`, `add`, `labels`) puts J1300, J102 and J800 on one row on the back (origins at y 63.0, pins on one line at y 64.95), redraws their AUX_3V3, I2C_SCL, I2C_SDA and RTC_BACKUP routes and centres the POWER / 3V3 I2C / RTC BACKUP labels on one line; `assembly_labels.py --prototype-silk` (U1201 under its part, J102 and J800 centred above their connectors), `check_silk_text.py`, DRC, `verify.py --a02`, `routing_audit.py --a02`, `fab_a02.py`.
  `design/release.py` holds the release state the output scripts print. `rework.py` and `route_a02.py seed` now refuse to run without `--rebuild`: both rebuild the board from earlier seeds.

Each routing script removes and redraws only the copper it owns. `tidy_routes.py` reshapes unlocked copper, so a hand script re-run after it no longer recognises its own routes: re-run hand scripts from a board saved before the tidy. In this KiCad build a `Remove()` leaves the Python bindings unreliable for the rest of the process, so the newer scripts remove, add and verify in separate runs. Helpers:
- `free_spot.py`: collision-checked placement of one part.
- `gnd_pad_vias.py`: a GND via beside a named pad (straight or 45-degree stub), or `A>B` to tie a GND pin to a grounded pad of the same part.
- `rip_box.py NET x0 y0 x1 y1`: removes a net's unlocked copper inside a box for re-routing.
- `handroute.py`: shared rip / place / add phases for the hand-route scripts (locked copper, 45-degree check).
- `clean_dangling.py`: removes track stubs.
- `drop_dangling.py`: removes exactly the items DRC reports as dangling; `--keep` spares named nets.
- `gnd_islands.py` / `gnd_stitch.py`: list and stitch GND pour fragments with no via. `gnd_islands.py` also lists fragments tied in only by a track or a pad's thermal spokes; DRC's unconnected count is the authority.
- `chamfer_a02_corners.py`: 45-degree chamfers on the right-angle bends `routing_audit.py` counts, locked copper included; run after `tidy_routes.py`.
- `grid_router.py`: `GR_ORDER=argv` routes the named nets in order, `GR_LIMIT` sets the search budget, `GR_DEBUG=<dir>` writes clear-cell masks, `GR_OUT` names the output, `GR_SKIP_REF=U700,...` leaves those parts' pads for designed routes.
- `regenerate_capture.py`: rebuilds schematic and BOM without touching the board.
- `route_secondary.py`: Freerouting export/import with existing copper fixed.

Never import a router session exported from different component positions or nets.

After circuit changes, regenerate the schematic, XML netlist, ERC and PDF. After board changes:
1. Run DRC with `--refill-zones --save-board`.
2. Run `verify.py --a02` and `routing_audit.py --a02`.
3. Inspect the copper and silk visually.

A passing checker does not validate power, thermal behaviour or physical fit.

Implementation stays in [issue #232](https://github.com/b5463/kino-d4/issues/232) and [ECN-0007](../../changes/ECN-0007-four-xiao-carrier-proposal.md), design package 0.1.8. The system power documents (`docs/audit/POWER_MODEL.md`, `docs/audit/HARDWARE_CONTRACT.md`) still describe the d4-v1 power path (SW6106 bank, 3 A harness); they change if this carrier is adopted.

The supplied ODD JOBS symbol and its traced contour remain reserved artwork, separate from CERN-OHL-S-2.0 hardware source. Stock KiCad footprints use the library electronic-design exception. Vendor design files are consulted, not redistributed. [Sources](SOURCES.md) records provenance. [A0.1 review](RELEASE-REVIEW.md) is kept as historical rejection evidence.

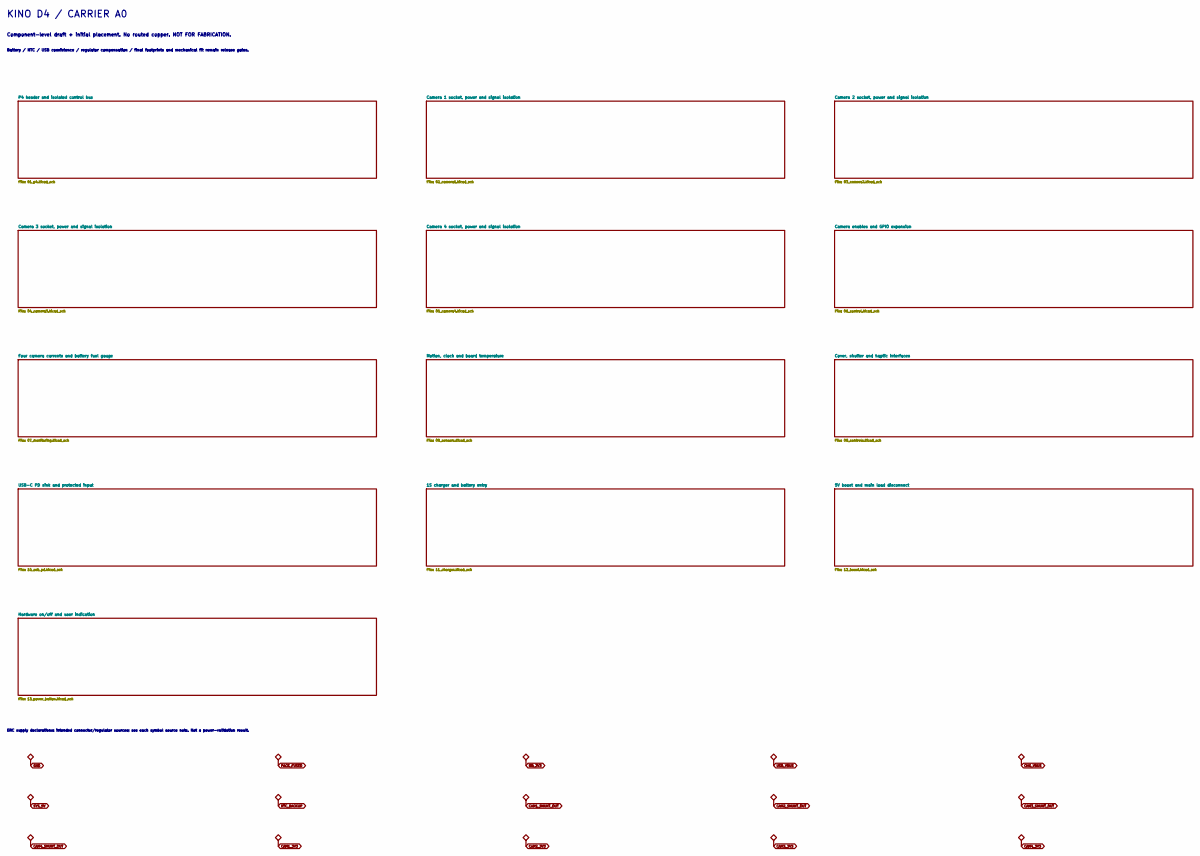
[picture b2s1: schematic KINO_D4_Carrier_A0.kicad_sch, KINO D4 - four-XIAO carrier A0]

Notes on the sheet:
KINO D4 / CARRIER A0
Component-level draft + initial placement. No routed copper. NOT FOR FABRICATION.
Battery / NTC / USB coexistence / regulator compensation / final footprints and mechanical fit remain release gates.
ERC supply declarations: intended connector/regulator sources; see each symbol source note. Not a power-validation result.
